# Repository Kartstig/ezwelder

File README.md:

# ezwelder
A simple adjustable spot welder

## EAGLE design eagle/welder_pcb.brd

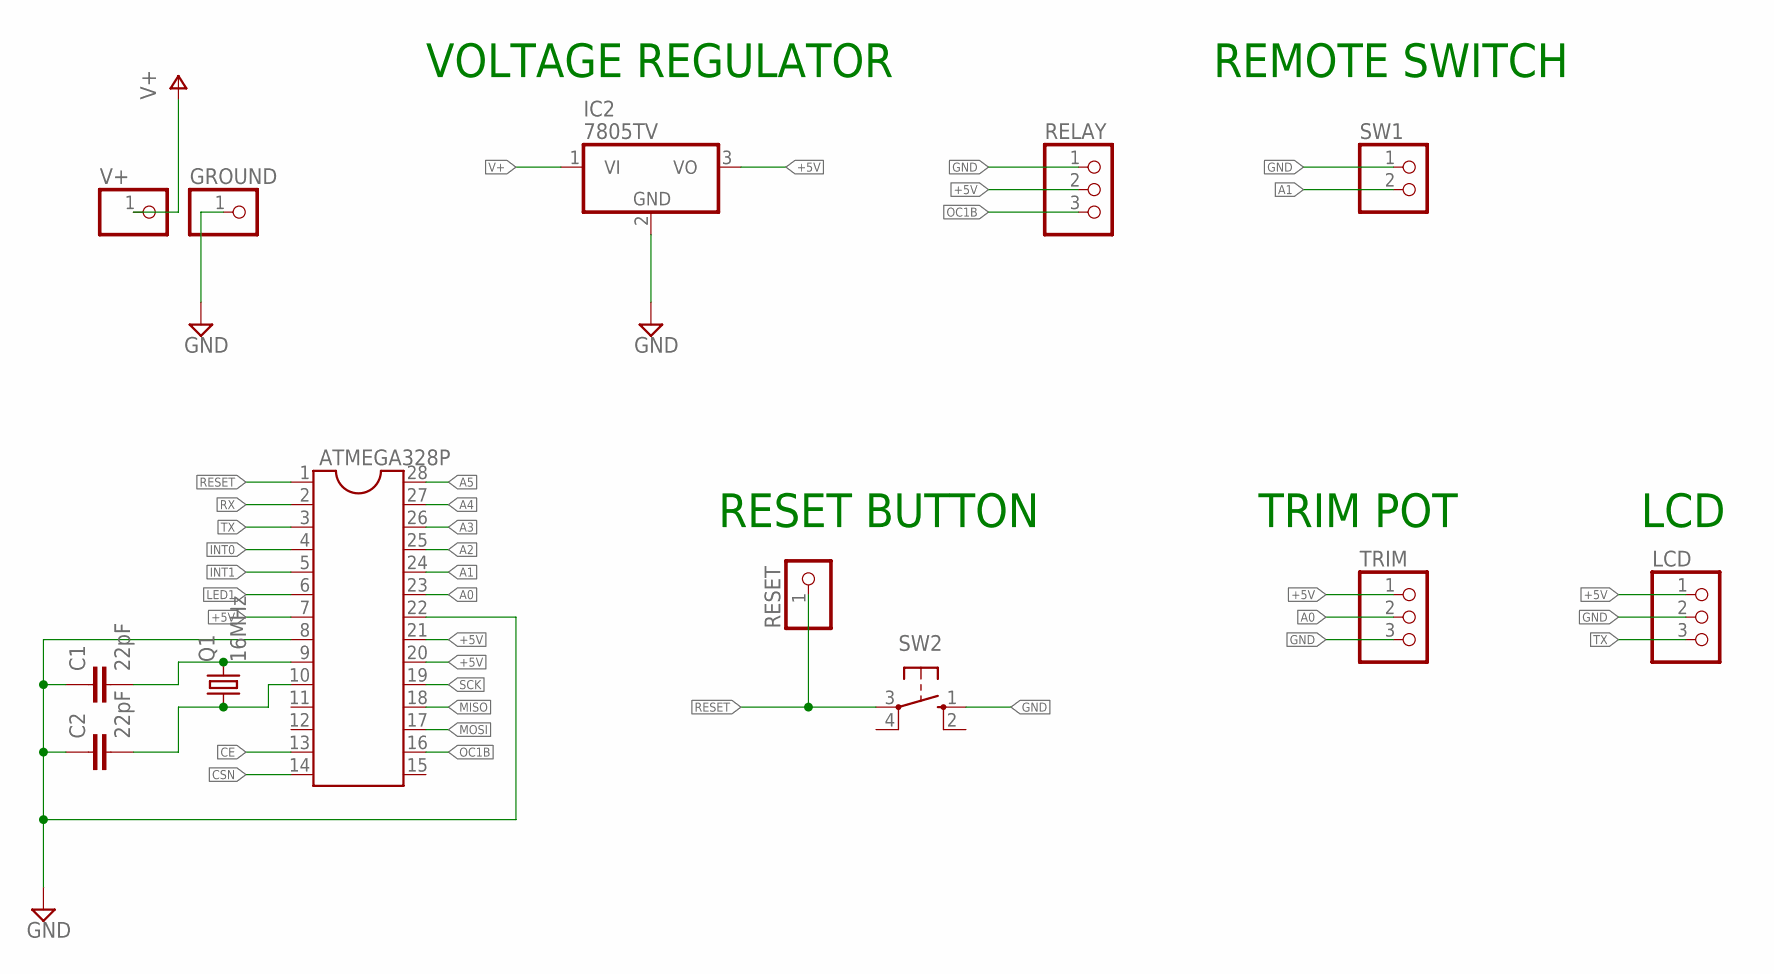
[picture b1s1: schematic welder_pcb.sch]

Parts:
ATMEGA328P: DIL28-3
C1, C2: 22pF; C2.5-3
GROUND: PINHD-1X1; 1X01
IC2: 7805TV; TO220V
LCD: PINHD-1X3; 1X03
Q1: 16MHz; HC49U-V
RELAY: PINHD-1X3; 1X03
RESET: PINHD-1X1; 1X01
SW1: PINHD-1X2; 1X02
SW2: 10-XX; B3F-10XX
TRIM: PINHD-1X3; 1X03
V+: PINHD-1X1; 1X01

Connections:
+5V: ATMEGA328P.7, ATMEGA328P.20, ATMEGA328P.21, IC2.3 (VO), LCD.1, RELAY.2, TRIM.1
A0: ATMEGA328P.23, TRIM.2
A1: ATMEGA328P.24, SW1.2
A2: ATMEGA328P.25
A3: ATMEGA328P.26
A4: ATMEGA328P.27
A5: ATMEGA328P.28
CE: ATMEGA328P.13
CSN: ATMEGA328P.14
GND: ATMEGA328P.8, ATMEGA328P.22, C1.1, C2.1, GROUND.1, IC2.2 (GND), LCD.2, RELAY.1, SW1.1, SW2.1 (S), TRIM.3
INT0: ATMEGA328P.4
INT1: ATMEGA328P.5
LED1: ATMEGA328P.6
MISO: ATMEGA328P.18
MOSI: ATMEGA328P.17
unnamed: ATMEGA328P.9, C1.2, Q1.2
unnamed: ATMEGA328P.10, C2.2, Q1.1
OC1B: ATMEGA328P.16, RELAY.3
RESET: ATMEGA328P.1, RESET.1, SW2.3
RX: ATMEGA328P.2
SCK: ATMEGA328P.19
TX: ATMEGA328P.3, LCD.3
V+: IC2.1 (VI), V+.1

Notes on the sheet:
RESET BUTTON
VOLTAGE REGULATOR
REMOTE SWITCH
LCD
TRIM POT

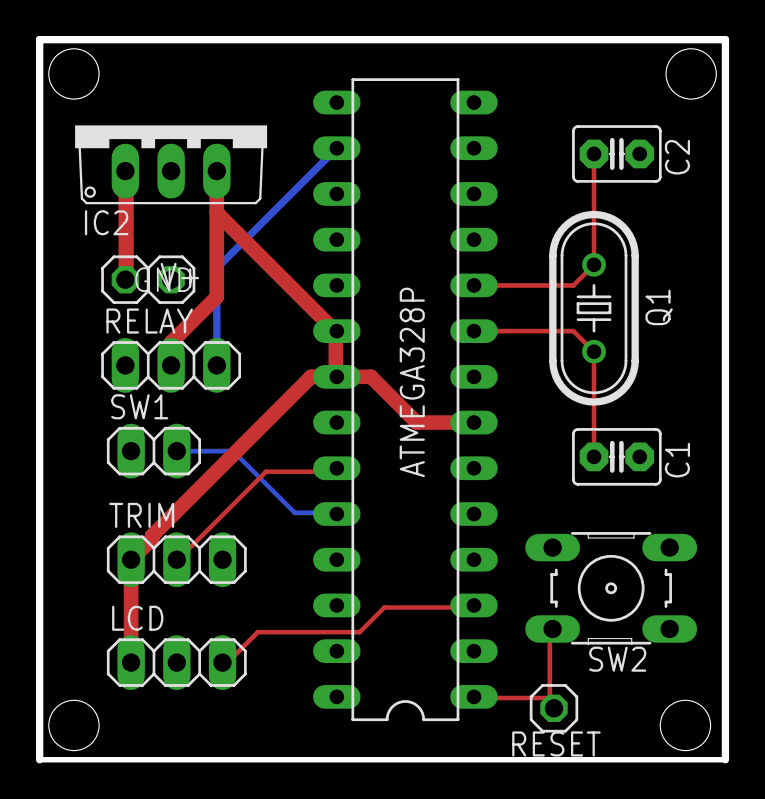
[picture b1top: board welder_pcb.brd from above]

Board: 2 copper layers, 38.1 x 40.0 mm, 13 parts (0 on the bottom side), 10 nets.

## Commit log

2018-10-02 Initial design
2018-10-02 Don't track eagle save points
2018-10-22 Add Relay Pins
